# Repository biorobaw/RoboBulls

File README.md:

This is a branch from the Robobulls repository that implements
neural networks for determining shooting probabilities and DDPG for reinforcement learning
for low level move-to-ball and shooting behaviors.

# Training Scripts
[Shot Predictor](https://github.com/justinandrewrodney/CanShootTrainer)

[Deep Reinforcment Learning trainer](https://github.com/justinandrewrodney/SSL_DDPG_rSoccer)

You will need libTensorflow and LibTorch(PyTorch C++) to run this project and update
their paths in the .pro file.

I had luck with the PyTorch precompiled binaries located [here](https://download.pytorch.org/libtorch/cu102/libtorch-win-shared-with-deps-debug-1.10.1%2Bcu102.zip).
I encountered issus when compiling LibTorch from source.

libTensorflow binaries can be found [here](https://www.tensorflow.org/install/lang_c).

# Main Changes

[attackmainNN.cpp](src/model/team/controllers/normal_game/behaviors/attackmainNN.cpp)

[gotoballRL.cpp](src/model/robot/behaviors/skills/gotoballRL.cpp)

[shoottogoalRL.cpp](src/model/robot/behaviors/skills/shoottogoalRL.cpp)

[gotoballandshootRL.cpp](src/model/robot/behaviors/skills/gotoballandshootRL.cpp)

robobulls2
==========

Narges super version of the new architecture for Williams robobulls

Documentation
-------------
See **docs/Robobulls Documentation.docx**

Installation
------------
See sections "Required Software" and "Compiling the code" in documentation file **docs/Robobulls Documentation.docx**
For instractions on how to install grSim (required softwre) on windows, see file **docs/Install grSim on windows.docx**

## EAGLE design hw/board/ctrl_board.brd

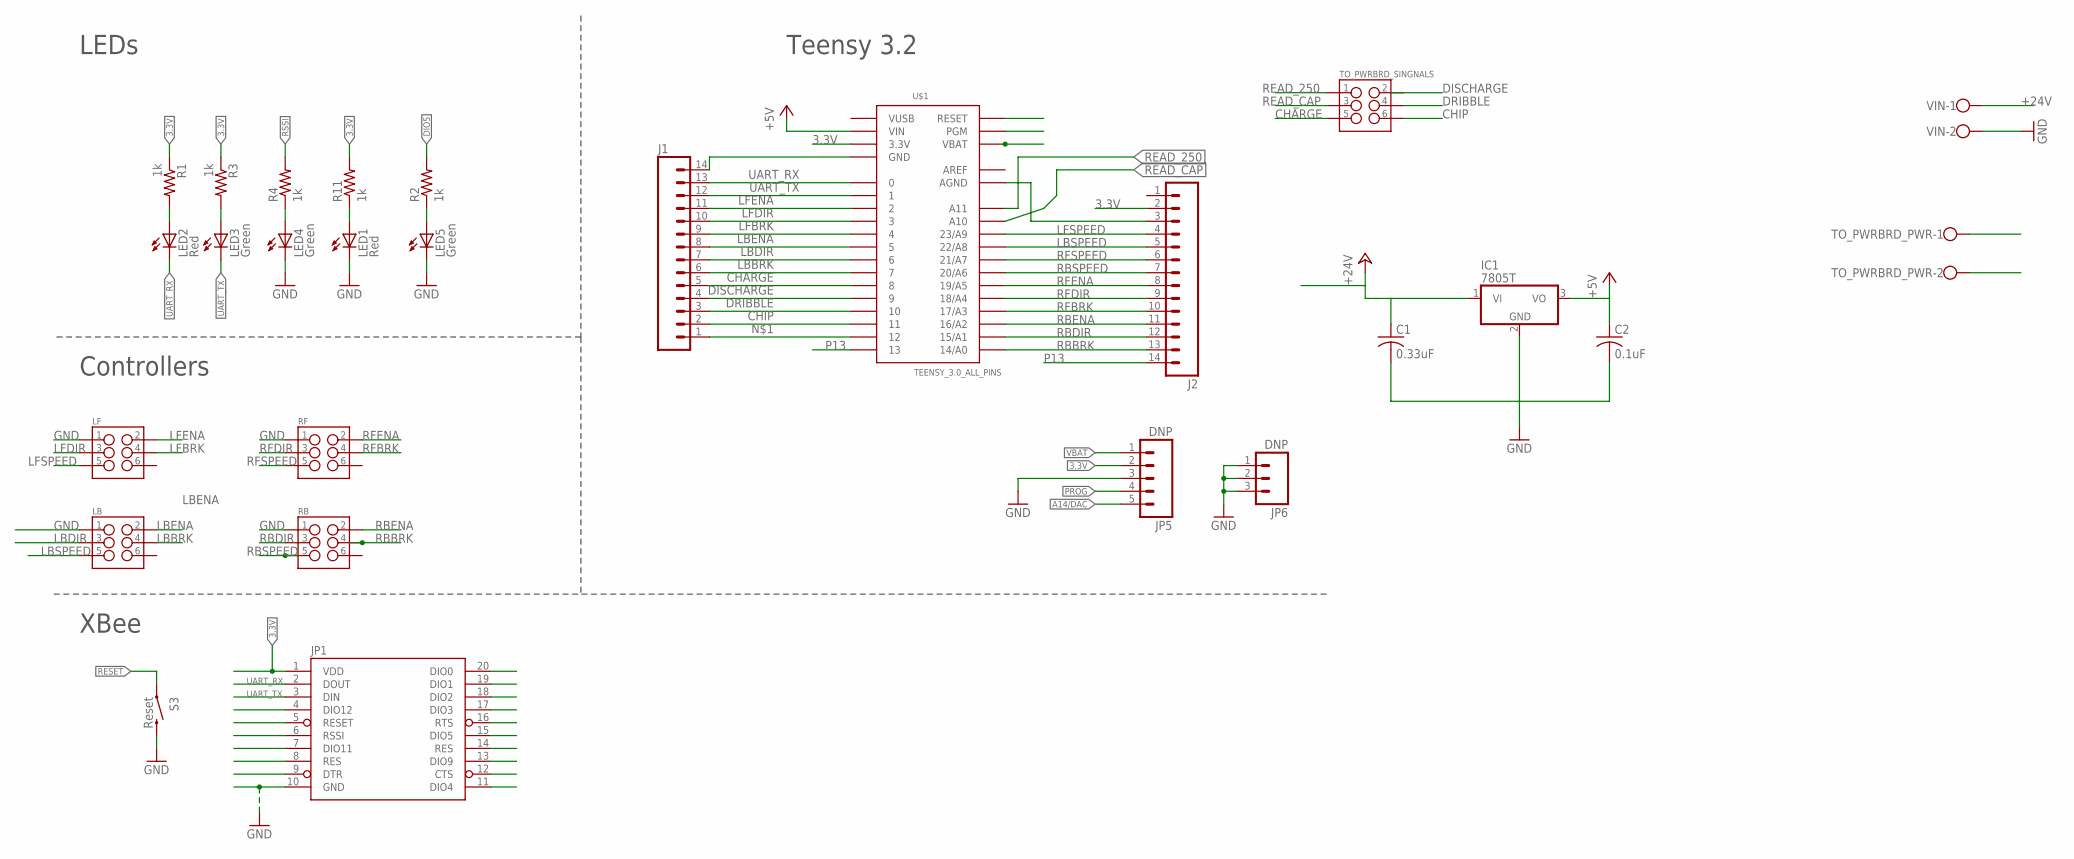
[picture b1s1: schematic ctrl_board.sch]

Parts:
C1: 0.33uF; C0805
C2: 0.1uF; C0805
IC1: 7805T; TO220H
J1, J2: M14; 1X14
JP1: XBEE-1B1; XBEE-1
JP5: DNP; 1X05
JP6: DNP; 1X03
LB: M03X2POGO_PINS; 2X3_POGO
LED1, LED2: Red; LED-0603
LED3, LED4, LED5: Green; LED-0603
LF: M03X2POGO_PINS; 2X3_POGO
R1, R2, R3, R4, R11: 1k; 0603-RES
RB: M03X2POGO_PINS; 2X3_POGO
RF: M03X2POGO_PINS; 2X3_POGO
S3: Reset; TACTILE-SWITCH-SMD
TO_PWRBRD_PWR: W237-102
TO_PWRBRD_SINGNALS: M03X2POGO_PINS; 2X3_POGO
U$1: TEENSY_3.0_ALL_PINS; TEENSY3-ALL_PINS
VIN: W237-102

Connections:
3.3V: J2.2, JP1.1 (VDD), JP5.2, R1.1, R3.1, R11.2, U$1.3.3V, U$1.3.3V1 (3.3V)
+5V: C2.1, IC1.3 (VO), U$1.VIN
+24V: C1.1, IC1.1 (VI), TO_PWRBRD_PWR.1, VIN.1; also elsewhere on the board
A14/DAC: JP5.5, U$1.RESET/DAC (RESET)
AREF: U$1.AREF
CHARGE: J1.5, TO_PWRBRD_SINGNALS.P$5 (5), U$1.8
CHIP: J1.2, TO_PWRBRD_SINGNALS.P$6 (6), U$1.11
CTS: JP1.12 (CTS)
DIO0: JP1.20 (DIO0)
DIO1: JP1.19 (DIO1)
DIO2: JP1.18 (DIO2)
DIO3: JP1.17 (DIO3)
DIO4: JP1.11 (DIO4)
DIO5: JP1.15 (DIO5), R2.2
DIO9: JP1.13 (DIO9)
DIO11: JP1.7 (DIO11)
DIO12: JP1.4 (DIO12)
DISCHARGE: J1.4, U$1.9
DRIBBLE: J1.3, TO_PWRBRD_SINGNALS.P$4 (4), U$1.10
DTR: JP1.9 (DTR)
GND: C1.2, C2.2, IC1.2 (GND), J1.14, JP1.10 (GND), JP5.3, JP6.1, JP6.2, JP6.3, LB.P$1 (1), LED1.C, LED4.C, LED5.C, LF.P$1 (1), RB.P$1 (1), RF.P$1 (1), S3.3 (2), TO_PWRBRD_PWR.2, U$1.GND, U$1.GND1 (GND), VIN.2; also elsewhere on the board
LBBRK: J1.6, LB.P$4 (4), U$1.7
LBDIR: J1.7, LB.P$3 (3), U$1.6
LBENA: J1.8, LB.P$2 (2), U$1.5
LBSPEED: J2.5, LB.P$5 (5), U$1.22/A8
LFBRK: J1.9, LF.P$4 (4), U$1.4
LFDIR: J1.10, LF.P$3 (3), U$1.3
LFENA: J1.11, LF.P$2 (2), U$1.2
LFSPEED: J2.4, LF.P$5 (5), U$1.23/A9
unnamed: J1.1, U$1.12
unnamed: LED1.A, R11.1
unnamed: LED2.A, R1.2
unnamed: J2.3, U$1.AGND
unnamed: LED3.A, R3.2
unnamed: LED4.A, R4.1
unnamed: LED5.A, R2.1
P13: J2.14, U$1.13
PROG: JP5.4, U$1.PGM
RBBRK: J2.13, RB.P$4 (4), U$1.14/A0
RBDIR: J2.12, RB.P$3 (3), U$1.15/A1
RBENA: J2.11, RB.P$2 (2), U$1.16/A2
RBSPEED: J2.7, RB.P$5 (5), U$1.20/A6
READ_250: TO_PWRBRD_SINGNALS.P$1 (1), U$1.A11
READ_CAP: TO_PWRBRD_SINGNALS.P$3 (3), U$1.A10
RES: JP1.8 (RES)
RES2: JP1.14 (RES)
RESET: JP1.5 (RESET), S3.1
RFBRK: J2.10, RF.P$4 (4), U$1.17/A3
RFDIR: J2.9, RF.P$3 (3), U$1.18/A4
RFENA: J2.8, RF.P$2 (2), U$1.19/A5
RFSPEED: J2.6, RF.P$5 (5), U$1.21/A7
RSSI: JP1.6 (RSSI), R4.2
RTS: JP1.16 (RTS)
UART_RX: J1.13, JP1.2 (DOUT), LED2.C, U$1.0
UART_TX: J1.12, JP1.3 (DIN), LED3.C, U$1.1
VBAT: JP5.1, U$1.VBAT
VUSB: U$1.VUSB

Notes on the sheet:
Teensy 3.2
XBee
Controllers
LEDs

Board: 2 copper layers, 31 parts (0 on the bottom side), 43 nets, no tracks yet.

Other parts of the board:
CTRL1+, CTRL2, CTRL3, CTRL4: W237-102

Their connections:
+24V: CTRL3.1, CTRL4.1; also elsewhere on the board
GND: CTRL1+.2, CTRL2.2, CTRL3.2; also elsewhere on the board
unnamed: CTRL1+.1, CTRL2.1

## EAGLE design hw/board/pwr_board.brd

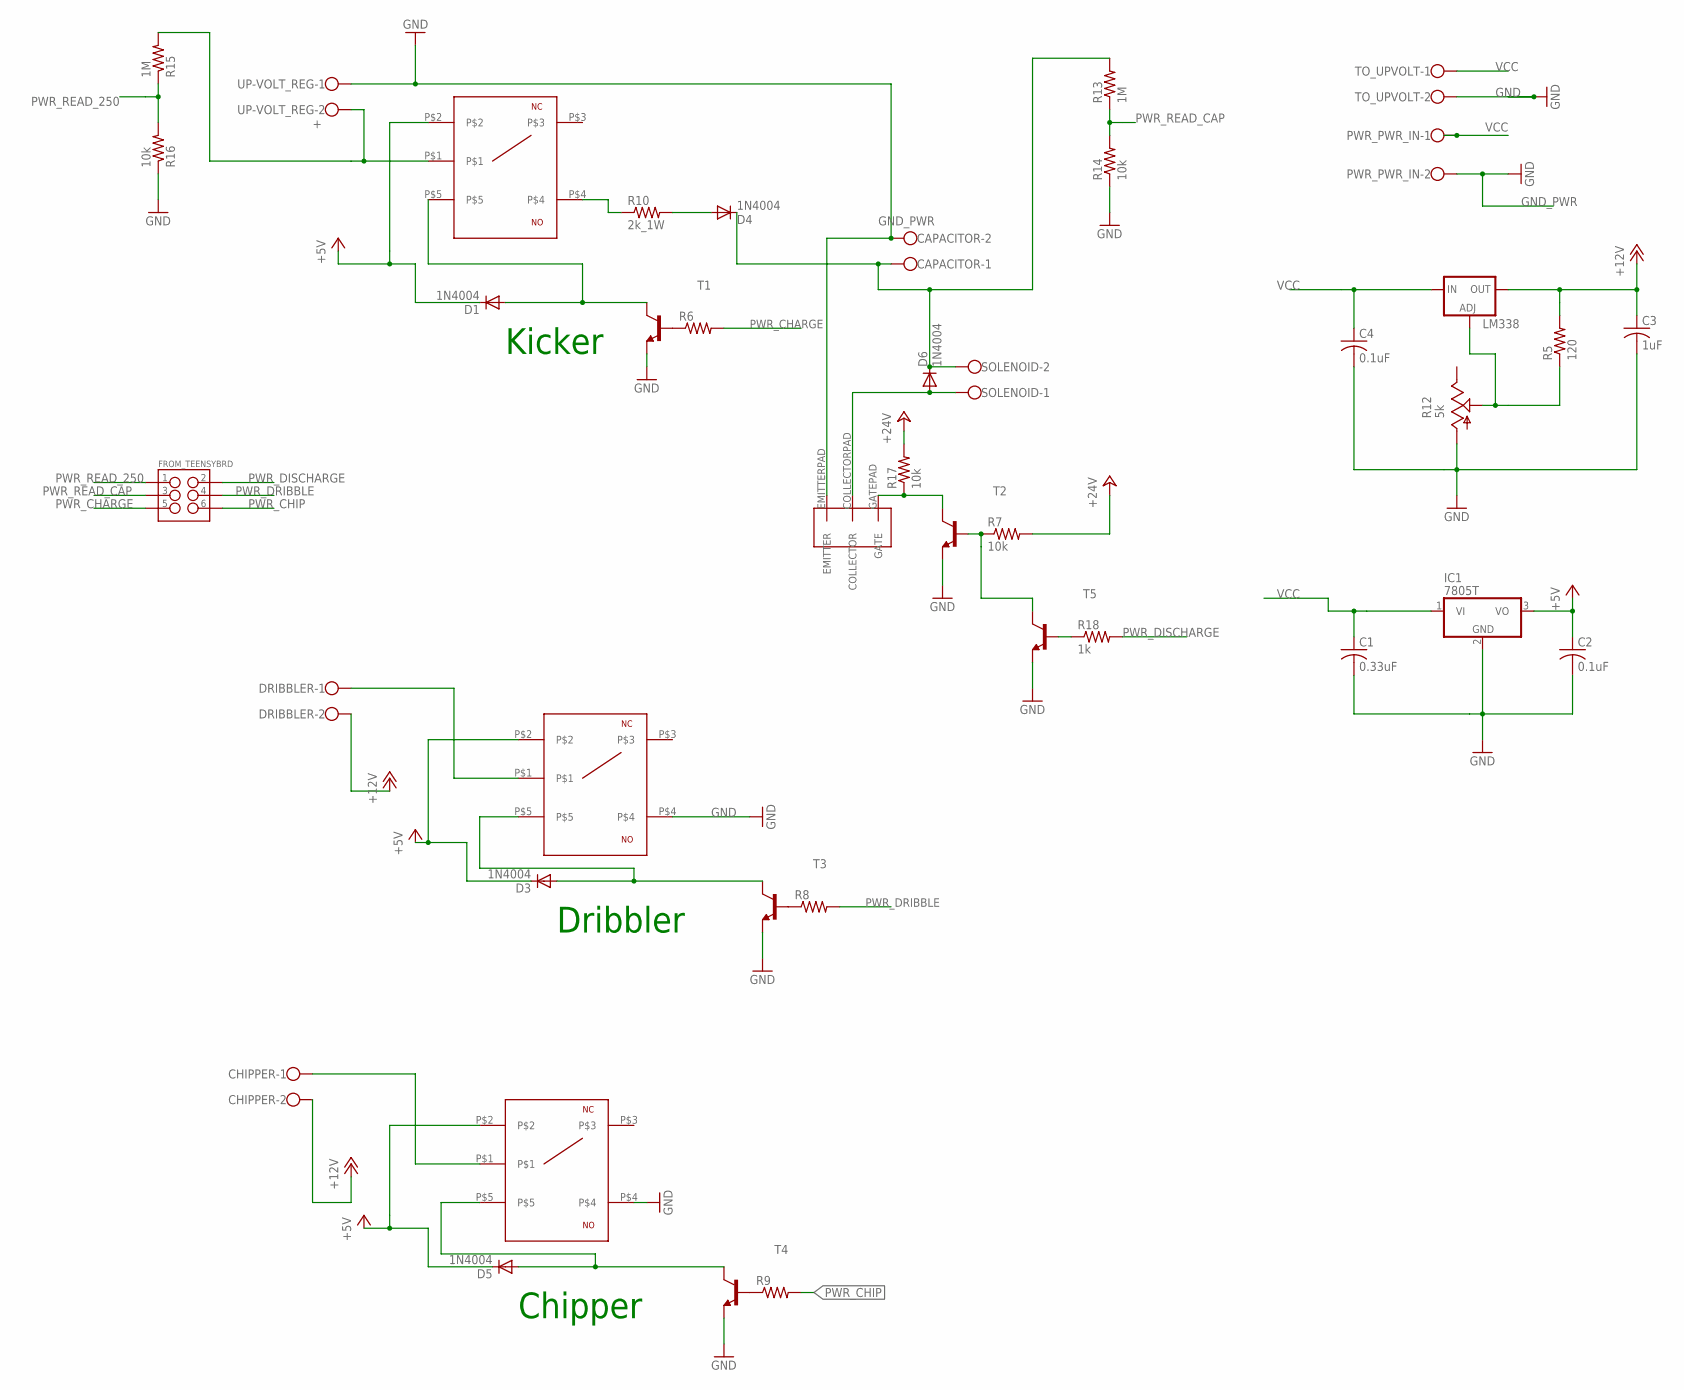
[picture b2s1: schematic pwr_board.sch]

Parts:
C1: 0.33uF; C0805
C2, C4: 0.1uF; C0805
C3: 1uF; C0805
CAPACITOR: W237-102
CHIPPER: W237-102
D1, D3, D4, D5, D6: 1N4004; DO41-10
DRIBBLER: W237-102
FROM_TEENSYBRD: M03X2POGO_PINS; 2X3_POGO
IC1: 7805T; TO220H
LM338: LM317TL; 317TL
PWR_PWR_IN: W237-102
R5: 120; M0805
R6, R8, R9: R-US_0207/7; 0207/7
R7, R17: 10k; 0207/7
R10: 2k_1W; 0309/12
R12: 5k; B25P
R13, R15: 1M; M0805
R14, R16: 10k; M0805
R18: 1k; 0207/7
SOLENOID: W237-102
T1, T2, T3, T4, T5: 2N3904-NPN-TO92-EBC; TO92-EBC
TO_UPVOLT: W237-102
U$2: APT75GN120LG; TO-264
U$3, U$4, U$5: PANASONIC_JS1
UP-VOLT_REG: +; W237-102

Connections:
+5V: C2.1, D1.C, D3.C, D5.C, IC1.3 (VO), U$3.P$2, U$4.P$2, U$5.P$2
+12V: C3.1, CHIPPER.2, DRIBBLER.2, LM338.2 (OUT), R5.2
+24V: R7.2, R17.2
GND: C1.2, C2.2, C3.2, C4.2, IC1.2 (GND), R12.A, R14.1, R16.1, T1.E, T2.E, T3.E, T4.E, T5.E, TO_UPVOLT.2, U$4.P$4, U$5.P$4
GND_PWR: CAPACITOR.2, PWR_PWR_IN.2, U$2.EMITTERPAD (EMITTER), UP-VOLT_REG.1
unnamed: LM338.1 (ADJ), R5.1, R12.S
unnamed: R18.1, T5.B
unnamed: R7.1, T2.B, T5.C
unnamed: R17.1, T2.C, U$2.GATEPAD (GATE)
unnamed: D1.A, T1.C, U$3.P$5
unnamed: D3.A, T3.C, U$4.P$5
unnamed: D4.A, R10.2
unnamed: R10.1, U$3.P$4
unnamed: D6.A, SOLENOID.1, U$2.COLLECTORPAD (COLLECTOR)
unnamed: CAPACITOR.1, D4.C, D6.C, R13.2, SOLENOID.2
unnamed: R15.2, U$3.P$1, UP-VOLT_REG.2
unnamed: R6.1, T1.B
unnamed: R8.1, T3.B
unnamed: DRIBBLER.1, U$4.P$1
unnamed: D5.A, T4.C, U$5.P$5
unnamed: R9.1, T4.B
unnamed: CHIPPER.1, U$5.P$1
PWR_CHARGE: FROM_TEENSYBRD.P$5 (5), R6.2
PWR_CHIP: FROM_TEENSYBRD.P$6 (6), R9.2
PWR_DISCHARGE: FROM_TEENSYBRD.P$2 (2), R18.2
PWR_DRIBBLE: FROM_TEENSYBRD.P$4 (4), R8.2
PWR_READ_250: FROM_TEENSYBRD.P$1 (1), R15.1, R16.2
PWR_READ_CAP: FROM_TEENSYBRD.P$3 (3), R13.1, R14.2
VCC: C1.1, C4.1, IC1.1 (VI), LM338.3 (IN), PWR_PWR_IN.1, TO_UPVOLT.1

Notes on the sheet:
Kicker
Dribbler
Chipper

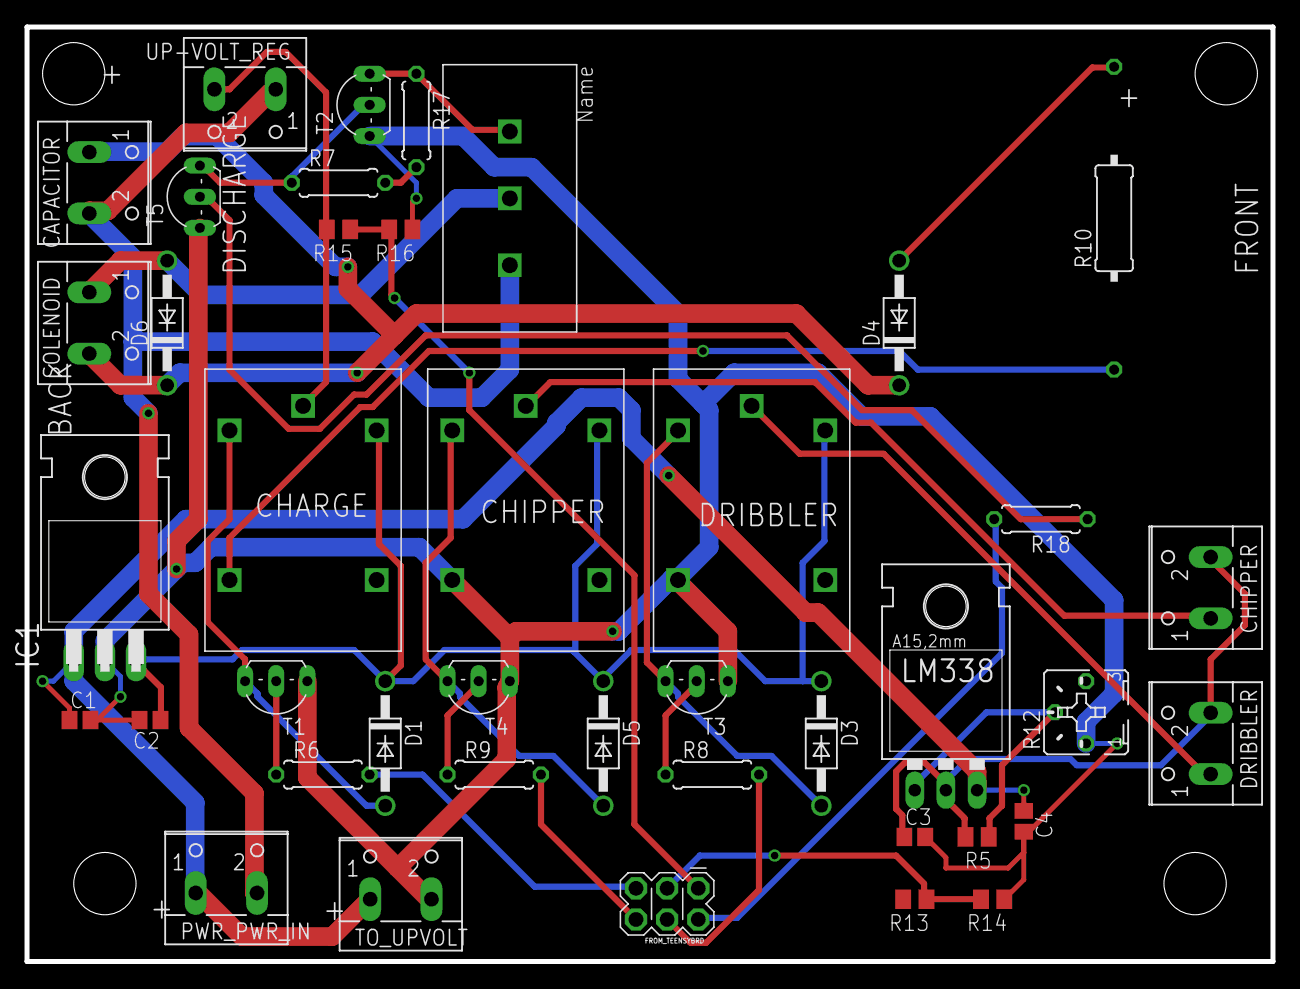
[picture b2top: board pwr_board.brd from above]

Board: 2 copper layers, 101.6 x 76.2 mm, 41 parts (0 on the bottom side), 29 nets.

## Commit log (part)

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2015-09-14 Fixed too wide formations in DefendBehavior
2015-09-14 Removed various unneeded dependencies on SIMULATED
2015-09-14 Updated Documentation
2015-09-16 Fixed small error in Documentation
2015-09-23 Added examples folder
2015-09-28 Fixed new bug in FourWheelCalculator and GMB
2015-09-29 Iterative small improvements to KTPO, AttackMain/Support
2015-10-01 Initial commit of coordinate frame abstraction
2015-10-02 Iterative fix to KickOffStrategy, choosing closest point
2015-10-05 Initial working version of coordinate frame changes
2015-10-07 Changed ID 5 to be fourWheelOmni, send 'k' instead of 1
2015-10-07 Added integral component to FourWheelCalculator
2015-10-13 Fixed dribble on robots, simulated and non-simulated
2015-10-16 Changed 5's type to always be fourWheelOmni
2015-10-19 Added new Arduino code and moved old
2015-10-19 Tuned FourWheelCalculator, KTPO, and goalie for new robots
2015-10-20 Added SIMULATED dep to FourWheelCalc, removed from types
2015-10-21 Set R1 kick and drib to active low
2015-10-22 Fixed bug in new ball reading. <= 0
2015-10-22 Disabled Vision delay and FourWheelCalc slowdown for now
2015-11-04 Greatly reduced KTPO false-negative kick rate. Improved all-around
2015-11-04 Previous commit did not include changes to NGS
2015-11-16 Added StaticMovementBehavior for controller-friendly single-point movement
2015-11-24 RotateOnPoint added to project, lowered tolerance
2015-11-24 Added Robot::hasKicker. Fixed Comparisons min_element bug. Sped up game to 1.5x
2015-11-24 Fixed SIMULATED in Robot::hasKicker
2015-12-03 Lowered the Y value of ball indicator so it would not interfere with collision status
2016-01-07 Robot1 Arduino: Changed Wiring
2016-01-08 Robot1 Arduino: Added Dribbler Stop
2016-01-25 Fixed the bearing dial that is displayed when a robot is selected.
2016-01-27 Arduino: Changed Comms to Serial1
2016-01-31 arduino changes
2016-02-02 Added Adriano Vision address to communication.h
2016-02-03 Added Teensy Arduino file
2016-02-03 Changes to disable dribblin/kicking, moves 4 motors from PC commands through Xbee. Don't know why the LF direction pin had to be inverted for them to work consistently. Needs some controller tuning (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
2016-02-15 Added kicking to teensy arduino file
2016-02-16 changed config to simulated
2016-02-16 added functionality to the joystick_map command line function
2016-02-17 KickToPoint 100%
2016-02-18 Enabled kicking for all overridden robots using joysticks
2016-02-19 Changed constants more
2016-02-20 Fix in macros due to merging
2016-03-23 Added basis for monitoring info on robot panel
2016-03-28 Completed functionality for the gameState monitoring on the robot panel
2016-03-29 Added functionality to the robotpanel to show the current strategy
2016-04-08 Beginning KF implementation
2016-04-11 Kalman filter no longer crashes, but GUI does not update past the first frame
2016-04-14 KFilter Works now. Reduced KFilter to velocity and position
2016-04-14 Kalman Filter Velocity WIP
2016-04-21 Added Kalman filter library to repo
2016-04-27 Fixed Measurements::linePoint, made goalie move to block a stationary ball instead of staying dead-center across the goal
2016-05-06 Added four camera simulator support and fixed some bugs with four camera inputs.
2016-05-11 Added Kalman library to install script
2016-05-13 Added probability Field to compute best point to shoot from
2016-05-19 Factored in clustering of opponent defenders in AttackMain
2016-05-19 Fixed AttackMain Bug when dribbling
2016-05-26 Added mutex for gui::draw_point. Made visioncomm wait for all four packets before running strats. Finished support attacker programming
2016-06-02 Syncing work from different folder
2016-06-09 Improved Passing
2016-06-13 Added skill for goalie to dribble the ball backwards
2016-06-13 Lab Tests 1
2016-06-18 Fixed some problems in defend behavior with James
2016-06-20 Goalie now kicks to farthest open teammate. Stop Strat now moves robots away only if necessary
2016-06-22 Modified teensy code to prevent ESC errors. Movement now sends stop signals when target threshold is reached.
2016-06-23 Removed many deprecated and duplicated behaviors
2016-06-29 Set field type on global config, robcomm now using NXTRobComm for simulations for testing
2016-06-29 adjust fps to something reasonable for 38400 25fps*60bytes*8bits/byte=12000bits
2016-07-01 Modified strategy flow so that behaviors are assigned properly at each transition. Disbaled movement collisions.
2016-08-06 Updated documentation on some Attack Behaviors
2016-09-20 FIxed a bug or something
2016-10-14 Modified install script to always export serial rules
2016-10-18 Tuned Acceleration Ramp for YisiBot
2016-10-20 Updated install script to export serial rules properly and added qtserialport lib
2016-10-24 separation in two boards - work in progress
2016-11-16 Extra credit commit
2016-11-18 Passing to a still robot.
2016-12-13 Regen protobuf files
2017-01-02 Added power connectors to ctrl board, fix pwr board error
2017-03-28 Fixed Obstacle avoidance crash for multiple robots by checking whether pathqueue is empty before popping first element. Removed distance check for old vs. new obstacles before recalculating path. Mov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
2017-04-07 Renamed gotopose private functions
2018-05-03 Added makefile
    Makefile will allow compilation even when QT Creator fails.
    Overrides qt creator when compile.
    In terminal: make
2018-05-03 Fixed a typo with the comm file
2018-05-03 Added missing function go to beh
    This was needed to fix the simulation
2018-05-03 Will work with YISI robot
2018-05-10 Fixed mistake in team.h
2018-06-07 Corrected robot roles and pitch side
2018-06-23 Major bugfix: Fixed drive functions to update model with bot velocity data
    four_wheel_omni_pilot now updates X/Y/AngVel data to robot data structures
    located in model/robot.h and model/robot.cpp, and
    called by yisicomm for transmission to physical bots. A new
    movement header (move_parameters.h) has been added for manipulating
    important movement values to tweak the bot's locomotion.
    Bot ID's have been altered for testing purposes.
2018-07-25 Preliminary documentation added
2020-01-23 Moved ssl code to libs folder. Replaced/added the new protos used by ssl software. Recompiled protos using current version of protoc. Fixed compiler error from casting capturing lambda function to fu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
2020-01-26 Created a class to represent the ball. The information about the ball is no longer stored in class GameModel
2020-01-27 Created class Field in model replacing field parameters. Removed concept of myGoal and opponentGoal and functionality was replaced by getGoal(field side) provided by the new class Field
2020-02-09 Proto files are now compiled automatically, must have probuf installed. Also protos were moved to ssl-vision ssl-game-controller and ssl-grsim folders accordingly.
2020-02-12 Fixed issues with placement of kalman header files. Also fixed issue with protobuf not working on some linux computers
2020-02-19 Refactored kfball: -Added a support class CircularBuffer -Renamed kfball to MyKalmanFilter and relocated it to ssl-vision folder -Updated ssl-vision listener accordingly
2020-03-04 Code restructured and added library Eigen. All robot dependent code is now under folder src/robot. Movement concept was replaced by the navigation module under the robot folder. Now we do not disting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
2020-03-10 **Modified strategy controller. It is now an abstract class and implements a state machine which decides which strategies to perform. State transition logic was moved from the strategies to the contr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
2020-03-10 Added missing dlls
2020-03-11 Project should now work on both linux (ubuntu) and windows. Final test required. If successful, then merge with master.
2020-04-02 Controllers fixed + Small restructure of Behavior. Robot Pilot requires improving control method + calibration for each robot. Currently vision thread (which controls the robots) does not run fast en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
2020-04-03 Guiscene was removed. Also, removed imports to files deleted in previous commit. Performance / multithreading issues still need to be assessed.
2020-04-06 Modified files to use forward declaration of class Robot instead of including header file
2020-04-07 switched includes by forward declarations for classes in folders 'parameters' and 'robot'
2020-04-27 subclassed frame for the robot frames on left gui panel
2020-05-16 removed game panel class and instead replaced it with a promoted frame (panel_game_info)
2020-05-17 fixed previous commit bug that file was removed but still imported in code
2020-05-18 simplified main window and divided its functionalities into its components. Preparing to replace the robotpanel with a promoted frame
2020-05-20 Fixed bug with finding which robot had the ball. Also continued simplifying the gui and restructuring the code. Only panel_field is missing and then reconnecting slots/funcitonality
2020-05-24 finished reimplementing removed features, only thing remaining now is code clean up
2020-05-24 finished cleaning up gui/graphics, moving onto gui/panels and style_sheets
2020-05-27 Finished simplifying the gui. Also updated the documentation. Preparing for merge
2020-06-01 Added missing document file to docs
2020-08-06 Removed print message 'doing path planning'
2020-08-15 Each team now runs in its own thread. Big restructuring was required. Need to reimplement joystick usage. Next, reimplement 'field side hypothesis' (assumption that the team is always assigned the ne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
2020-08-16 chaged type of communication from poling to signals between RobotTeam and GuiTeams. Also refactored more code
2020-08-17 Fixing robot control
2020-08-18 Path planning and navigating to a coordinates was reenabled
2020-08-18 added missing semi-colon
2020-08-20 Left config in strategy tester
2020-08-20 Continued moving files
2020-12-04 Simplified path planner code
2021-01-15 Fixed bug in path planner, deciding when a robot considers a deffence area as an obstacle
2021-05-21 Bug fix, game controller thread was never started
2021-06-29 side change issue solved
2021-07-02 fixed attacksupport
2021-07-09 Added call to create Proxy for PiRobot2019
2021-07-09 Lines added to support PiRobot protobuff and controllers
2021-07-09 Revert "Rpi support"
    This reverts commit 61c0f9f54970a6b491129196985af8089fe6d3f2.
2021-07-14 Added robots map to store IP addr and port
2021-07-16 Attempting to get differential drive to work.
2021-07-20 normal game bug fixes
2021-08-03 Added ball placement strategy.
2021-08-09 update on config menu
2021-08-12 started validating behaviors
2021-08-17 started validating strategies
2021-08-20 update2
2021-08-27 update in AttackMain
2021-09-25 Fixed issue with infinitely decrementing defence area length
2021-11-05 Increased a tolerance for shooting(avoid hitting other robots)
2021-11-06 Fixed probability field
2021-11-06 Commented out print statements
2021-11-06 Fix probability field(uninitialized node probs result in bad values)
2021-11-20 commented some print statements
2021-11-20 Fixed in field function. Doesnt detect robots outside field
2021-11-20 removed testing comment(passing testing)
2021-12-14 Revised state changes and more synchronized passing
2021-12-17 Added NN and RL controllers
2021-12-17 push for backup before serious revision
2021-12-17 Revert "changes before reversion"
    This reverts commit b92688eb798196f220162803244c22fff9e28ecc.
2021-12-17 Revert "Added NN and RL controllers"
    This reverts commit 734cc94e753d2badef7486cdb6c69a207f51548d.
2021-12-20 added loose factory constructor structure to allow Behaviors to be swapped out. soon to be implemented using config files
2022-01-12 Adding different test and perform functions for easier readability
2022-01-26 fixed ssl_vision_listener line, turn off robots in grsim instead
2022-02-04 added TFlow
2022-02-04 Modifications for testing
2022-02-05 Fix ktpo num 2
2022-02-23 Fixed tolerance issues in dribble to point
2022-02-23 More includes for new behaviors
2022-02-23 Commented out prints
2022-02-23 commented out break statements
2022-04-06 Timer for thesis
2022-04-06 Linking libraries
2022-04-06 Comment out prints on dribble behavior
2022-04-06 Fix logic issues in ktpo

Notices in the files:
parts and their libraries:
SparkFun-Connectors: Licensing: Creative Commons ShareAlike 4.0 International - https://creativecommons.org/licenses/by-sa/4.0
